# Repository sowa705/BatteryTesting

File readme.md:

# Simple battery testing tool

This project aims to build a **complete** and affordable setup for DIY battery testing.

## Features

* Compatible with various battery types
* Battery capacity testing
* Internal resistance measurement
* Nice graphs
* Minimal component count, low cost

## Example test result

## Required parts

* Computer with Python 3
* Arduino Uno
* Constant current load (example schematic included in the hardware directory)

## Usage

* Connect all parts together (load is not applied until the software is started)
* Start the measurement with `python .\desktop\measurebattery.py [COM PORT] [CUTOFF VOLTAGE]`
* Battery will be discharged until it reaches specified voltage or *2.8V* if no voltage was specified
* Enter your battery name in the first line of the resulting file ( `battery_[TIME].txt` )
* Render the graph with `python .\desktop\rendergraph.py [FILE NAME]`

## Accuracy

Measurement accuracy depends heavily on how stable your PC USB voltage is, after calibration you should be able to get around 5% accuracy for capacity.

Accurate measurement of internal resistance requires good battery connection and good PCB design for your constant current load, stock design should be able to measure within 10%.

## Contributing

Contributions are welcome, feel free to submit your own test results or hardware/software improvements.

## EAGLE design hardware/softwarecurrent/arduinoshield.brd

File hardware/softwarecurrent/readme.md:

# Software current control board design

This directory contains the Eagle PCB design files for the Arduino shield with all required hardware installed

## Features

* Arduino shield format
* Software adjustable load
* Wide voltage range (0V - 50V)
* Active cooling

## Support

This PCB isn't yet supported as i wait for it to ship from China, this page will be updated when i get the software and hardware ready to use.

BOM and additional information will be available soon.

## Usage

**If your battery voltage exceeds 5V set the voltage switch to the "50V" position to enable the voltage divider.**

Connect your battery to the XT30 connector on the board, all further setup is done through software.

## Considerations

* This board heavily depends on reliable 5V power supply for the Arduino, with unstable voltage your results may drift considerably
* Watch out for the mosfet temperature, while this board has a fan connector you can easily overload it by discharging high currents from high voltage batteries

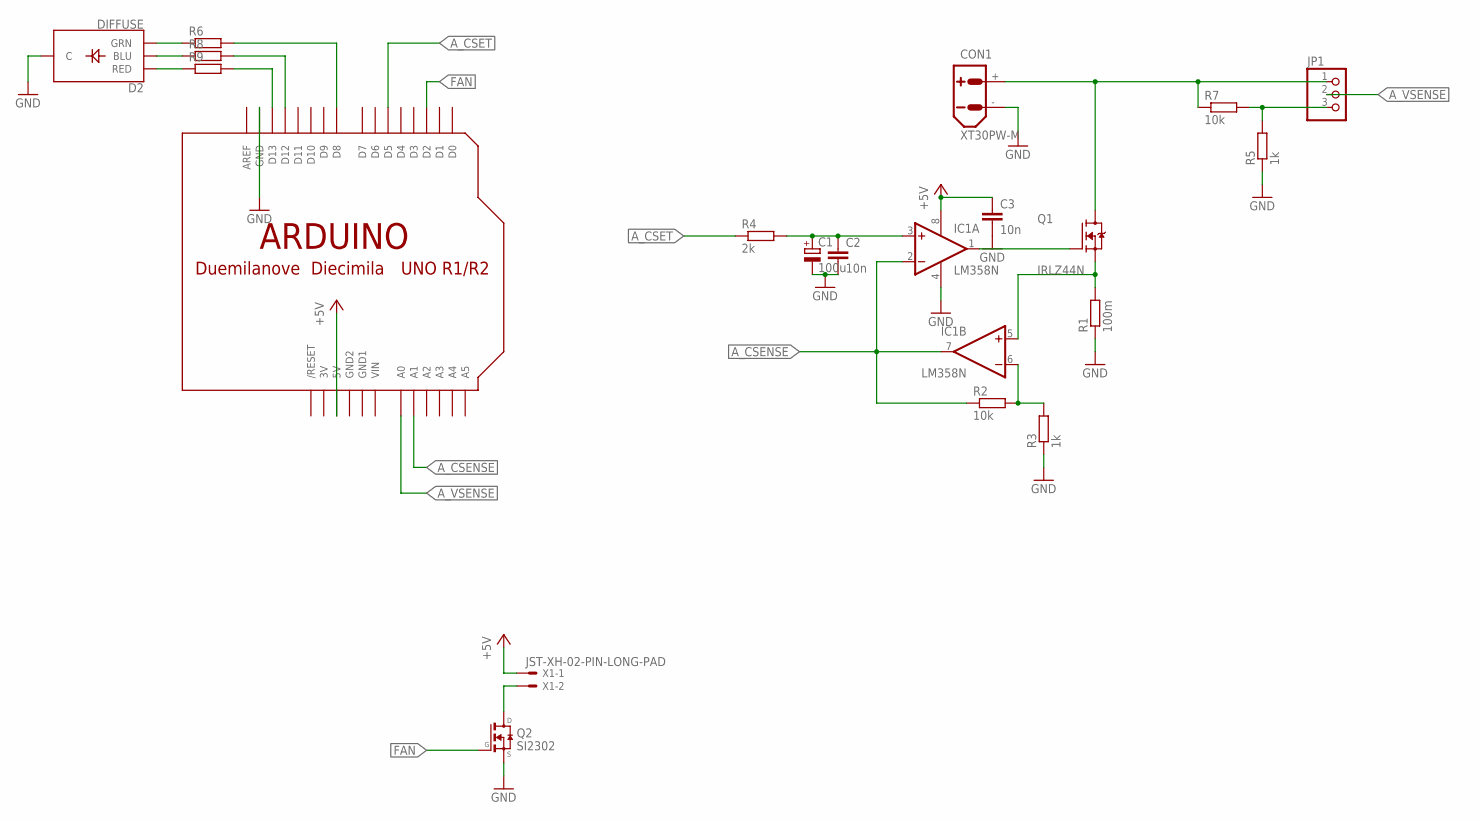
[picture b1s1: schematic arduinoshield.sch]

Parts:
C1: 100u; E2,5-7
C2, C3: 10n; C050-025X075
CON1: XT30PW-M
D2: DIFFUSE; LED-RGB-THRU
IC1: LM358N; DIL08
JP1: PINHD-1X3; 1X03
Q1: IRLZ44N; TO254P1054X469X1930-3
Q2: SI2302; SOT23
R1: 100m; R2512
R2, R7: 10k; M1206
R3, R5: 1k; M1206
R4: 2k; M1206
R6, R8, R9: R-EU_M1206; M1206
U$2: ARDUINO-NOHOLE
X1: JST-XH-02-PIN-LONG-PAD; JST-XH-02-PACKAGE-LONG-PAD

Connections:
3V: U$2.3V
+5V: C3.1, IC1.8 (V+), U$2.5V, X1.1
A_CSENSE: IC1.2 (-IN), IC1.7 (OUT), R2.1, U$2.A1
A_CSET: R4.1, U$2.D5
A_VSENSE: JP1.2, U$2.A0
FAN: Q2.1 (G), U$2.D2
GND: C1.-, C2.2, C3.2, CON1.-, D2.2 (C), IC1.4 (V-), Q2.2 (S), R1.1, R3.1, R5.1, U$2.GND
GND1: U$2.GND1
GND2: U$2.GND2
unnamed: IC1.5 (+IN), Q1.3 (S), R1.2
unnamed: CON1.+, JP1.1, Q1.2 (D), R7.1
unnamed: JP1.3, R5.2, R7.2
unnamed: IC1.1 (OUT), Q1.1 (G)
unnamed: C1.+, C2.1, IC1.3 (+IN), R4.2
unnamed: IC1.6 (-IN), R2.2, R3.2
unnamed: Q2.3 (D), X1.2
unnamed: D2.3 (GRN), R6.1
unnamed: D2.4 (BLU), R8.1
unnamed: D2.1 (RED), R9.1
unnamed: R6.2, U$2.D8
unnamed: R8.2, U$2.D12
unnamed: R9.2, U$2.D13
VIN: U$2.VIN

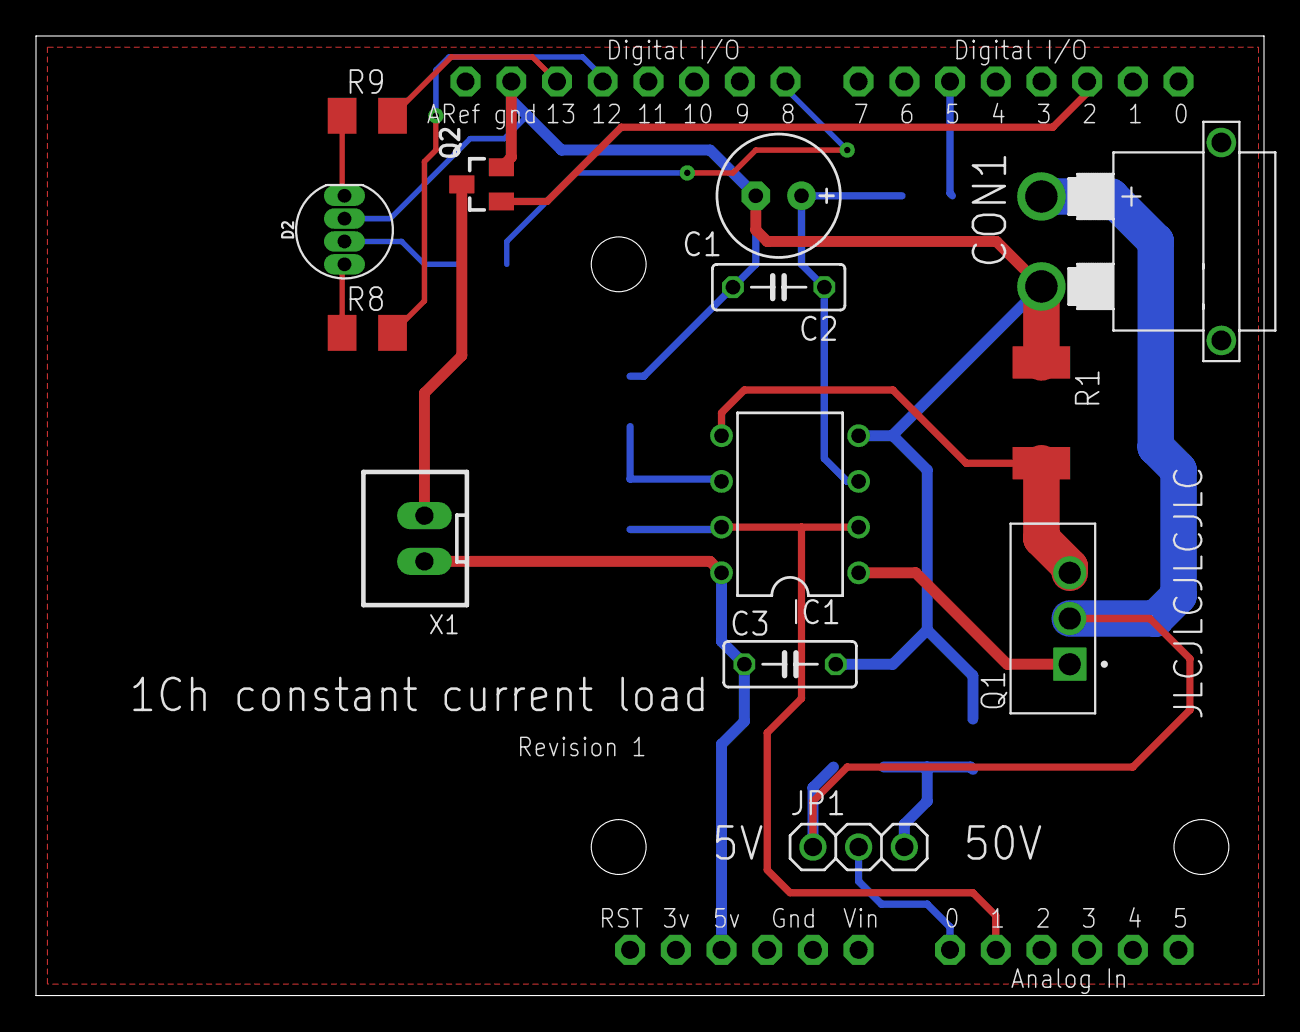
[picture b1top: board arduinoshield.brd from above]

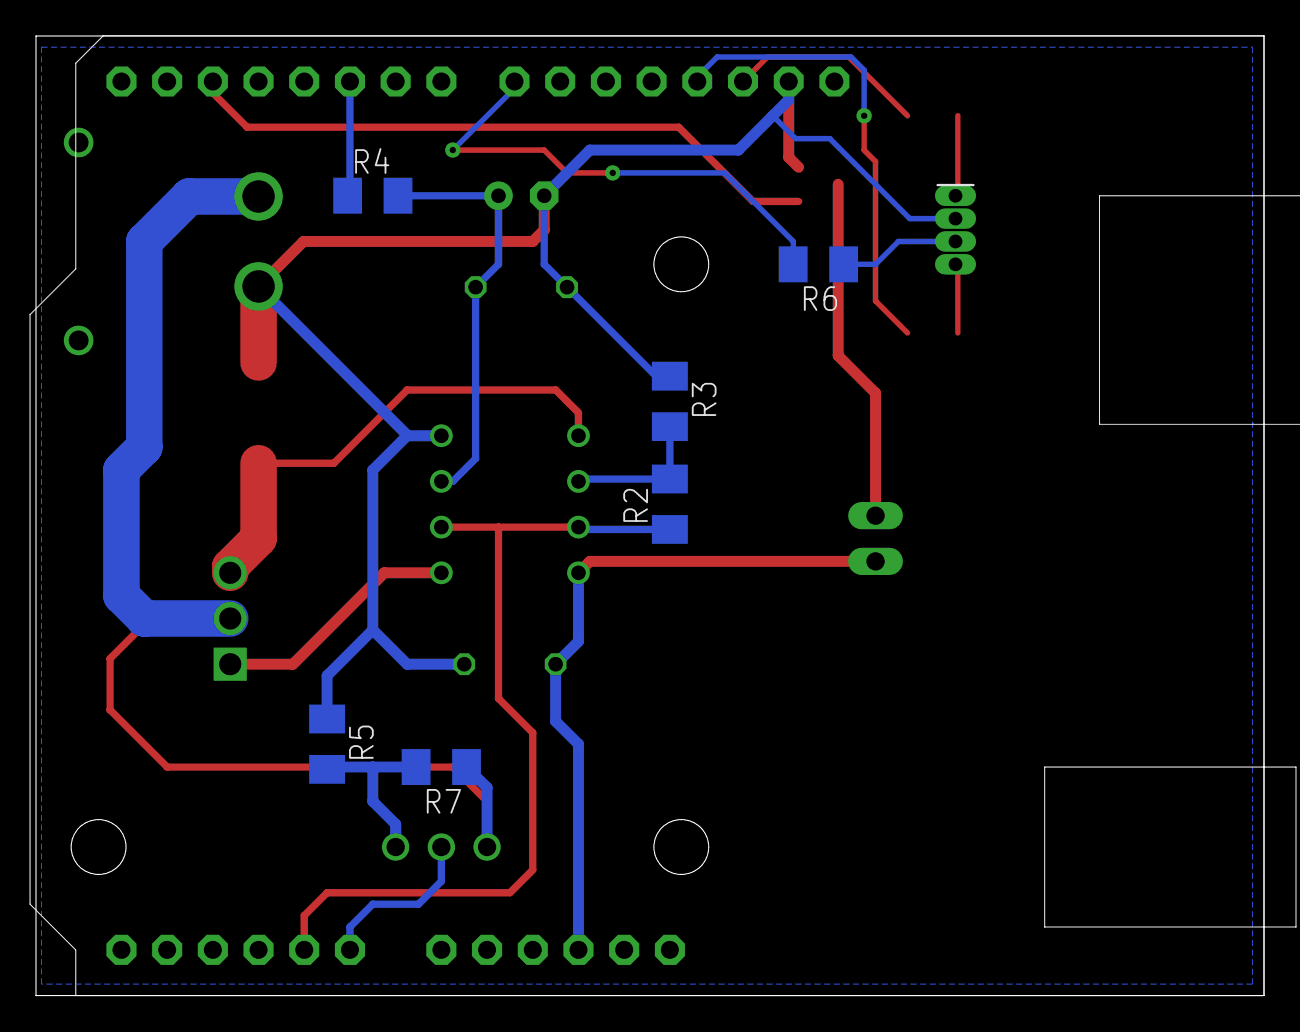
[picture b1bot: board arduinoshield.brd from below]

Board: 2 copper layers, 68.2 x 53.3 mm, 20 parts (6 on the bottom side), 19 nets.

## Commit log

2022-02-17 Delete battery.py
    duplicate file
2022-02-17 LGDB218650 battery added
2022-02-18 additional information

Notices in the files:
parts and their libraries:
SparkFun-LED: Licensing: Creative Commons ShareAlike 4.0 International - https://creativecommons.org/licenses/by-sa/4.0
